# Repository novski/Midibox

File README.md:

VLR - Midibox
==============

Welcome 

Im Building Midibox Parts since 2010. All my Layouts and Parts are available here soon.

You can use all my designs under the TAPR License: http://www.ucapps.de/TAPR_Noncommercial_Hardware_License_v1.0.pdf.

the source of this work is to find at www.ucapps.com

You can find involved people at www.midibox.org/forums

Partslists are in Progress..

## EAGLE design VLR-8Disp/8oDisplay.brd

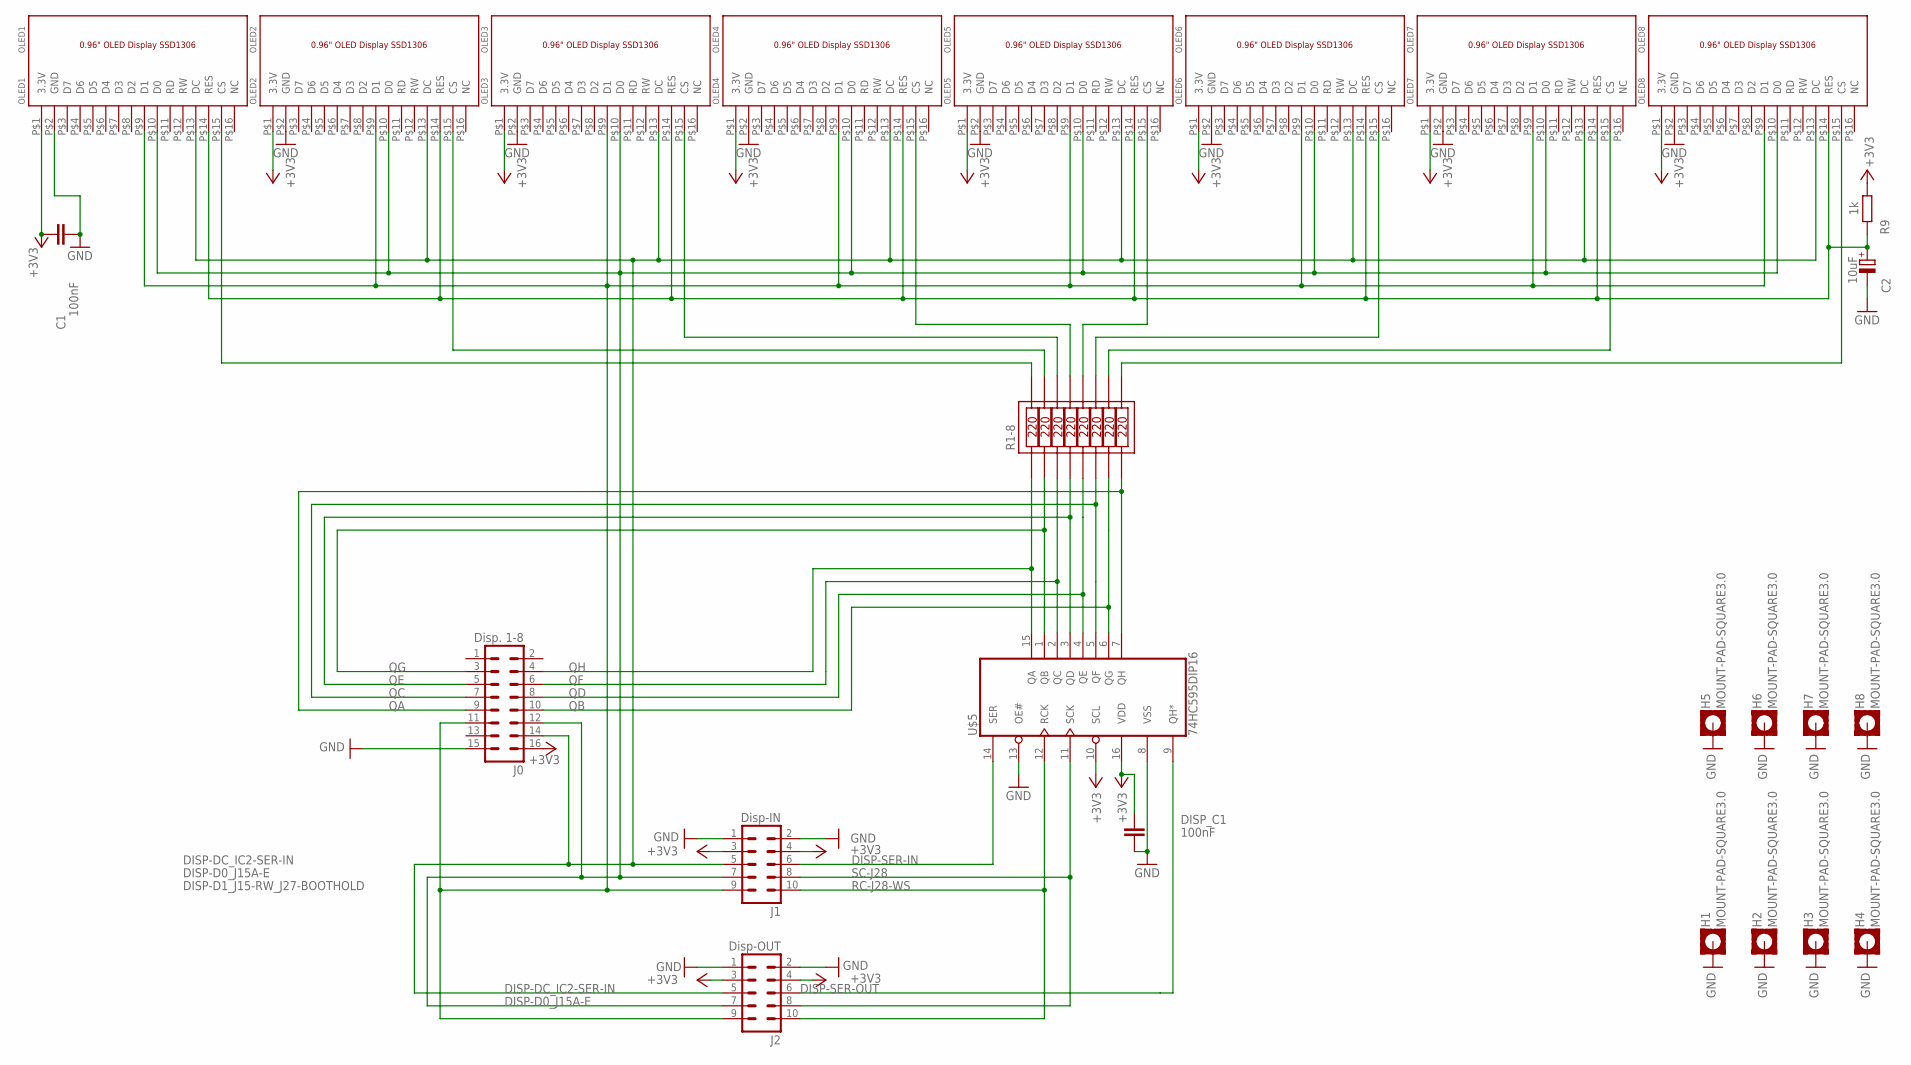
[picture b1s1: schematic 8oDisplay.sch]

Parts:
C1: 100nF; C5B3
C2: 10uF; E2,5-6
DISP_C1: 100nF; C5B3
H1, H2, H3, H4, H5, H6, H7, H8: MOUNT-PAD-SQUARE3.0; 3,0-PAD-SQUARE
J0: Disp. 1-8; ML16
J1: Disp-IN; ML10
J2: Disp-OUT; ML10
OLED1: OLED1; 0.96"
OLED2: OLED2; 0.96"
OLED3: OLED3; 0.96"
OLED4: OLED4; 0.96"
OLED5: OLED5; 0.96"
OLED6: OLED6; 0.96"
OLED7: OLED7; 0.96"
OLED8: OLED8; 0.96"
R1-8: 4116R; DIL16
R9: 1k; 0204/7
U$5: 74HC595DIP16; DIL16

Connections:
+3V3: C1.1, DISP_C1.1, J0.16, J1.3, J1.4, J2.3, J2.4, OLED1.P$1 (3.3V), OLED2.P$1 (3.3V), OLED3.P$1 (3.3V), OLED4.P$1 (3.3V), OLED5.P$1 (3.3V), OLED6.P$1 (3.3V), OLED7.P$1 (3.3V), OLED8.P$1 (3.3V), R9.2, U$5.10 (SCL), U$5.16 (VDD)
DISP-D0_J15A-E: J0.12, J1.7, J2.7, OLED1.P$10 (D0), OLED2.P$10 (D0), OLED3.P$10 (D0), OLED4.P$10 (D0), OLED5.P$10 (D0), OLED6.P$10 (D0), OLED7.P$10 (D0), OLED8.P$10 (D0)
DISP-D1_J15-RW_J27-BOOTHOLD: J0.11, J1.9, J2.9, OLED1.P$9 (D1), OLED2.P$9 (D1), OLED3.P$9 (D1), OLED4.P$9 (D1), OLED5.P$9 (D1), OLED6.P$9 (D1), OLED7.P$9 (D1), OLED8.P$9 (D1)
DISP-DC_IC2-SER-IN: J0.14, J1.5, J2.5, OLED1.P$13 (DC), OLED2.P$13 (DC), OLED3.P$13 (DC), OLED4.P$13 (DC), OLED5.P$13 (DC), OLED6.P$13 (DC), OLED7.P$13 (DC), OLED8.P$13 (DC)
DISP-SER-IN: J1.6, U$5.14 (SER)
DISP-SER-OUT: J2.6, U$5.9 (QH*)
GND: C1.2, C2.-, DISP_C1.2, H1.B3,0, H2.B3,0, H3.B3,0, H4.B3,0, H5.B3,0, H6.B3,0, H7.B3,0, H8.B3,0, J0.15, J1.1, J1.2, J2.1, J2.2, OLED1.P$2 (GND), OLED2.P$2 (GND), OLED3.P$2 (GND), OLED4.P$2 (GND), OLED5.P$2 (GND), OLED6.P$2 (GND), OLED7.P$2 (GND), OLED8.P$2 (GND), U$5.8 (VSS), U$5.13 (OE#)
QA: J0.9, R1-8.16, U$5.7 (QH)
QAA: OLED8.P$15 (CS), R1-8.8
QB: J0.10, R1-8.15, U$5.6 (QG)
QBB: OLED7.P$15 (CS), R1-8.7
QC: J0.7, R1-8.14, U$5.5 (QF)
QCC: OLED6.P$15 (CS), R1-8.6
QD: J0.8, R1-8.13, U$5.4 (QE)
QDD: OLED5.P$15 (CS), R1-8.5
QE: J0.5, R1-8.12, U$5.3 (QD)
QEE: OLED4.P$15 (CS), R1-8.4
QF: J0.6, R1-8.11, U$5.2 (QC)
QFF: OLED3.P$15 (CS), R1-8.3
QG: J0.3, R1-8.10, U$5.1 (QB)
QGG: OLED2.P$15 (CS), R1-8.2
QH: J0.4, R1-8.9, U$5.15 (QA)
QHH: OLED1.P$15 (CS), R1-8.1
RC-J28-WS: J1.10, J2.10, U$5.12 (RCK)
RST: C2.+, OLED1.P$14 (RES), OLED2.P$14 (RES), OLED3.P$14 (RES), OLED4.P$14 (RES), OLED5.P$14 (RES), OLED6.P$14 (RES), OLED7.P$14 (RES), OLED8.P$14 (RES), R9.1
SC-J28: J1.8, J2.8, U$5.11 (SCK)

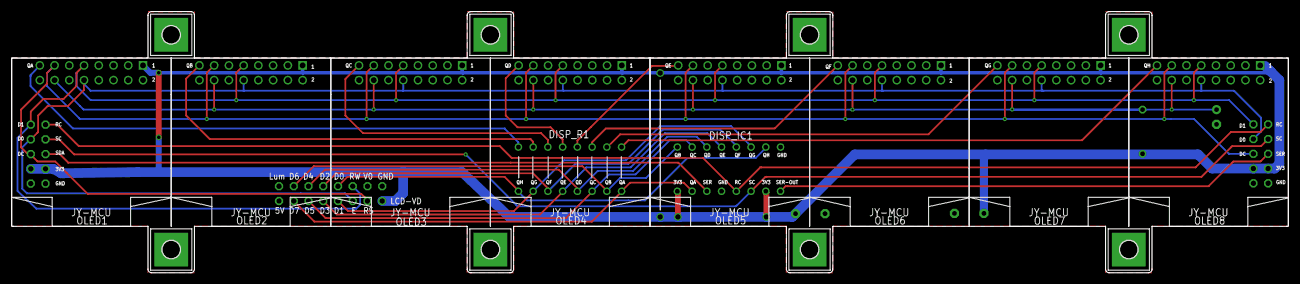
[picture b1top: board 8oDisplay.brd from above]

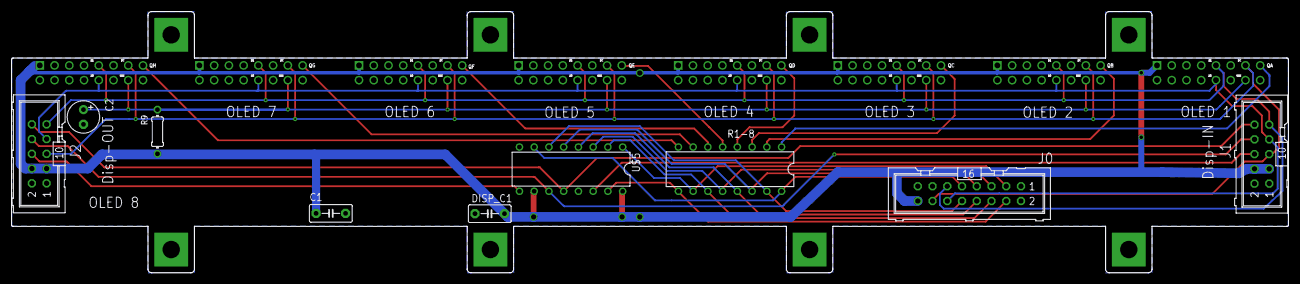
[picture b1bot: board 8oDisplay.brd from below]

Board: 2 copper layers, 220.0 x 45.0 mm, 28 parts (12 on the bottom side), 26 nets.

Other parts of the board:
U$1: X8ODISPLAY
U$2: VLRLAB
U$4: (C)T.KLOSE

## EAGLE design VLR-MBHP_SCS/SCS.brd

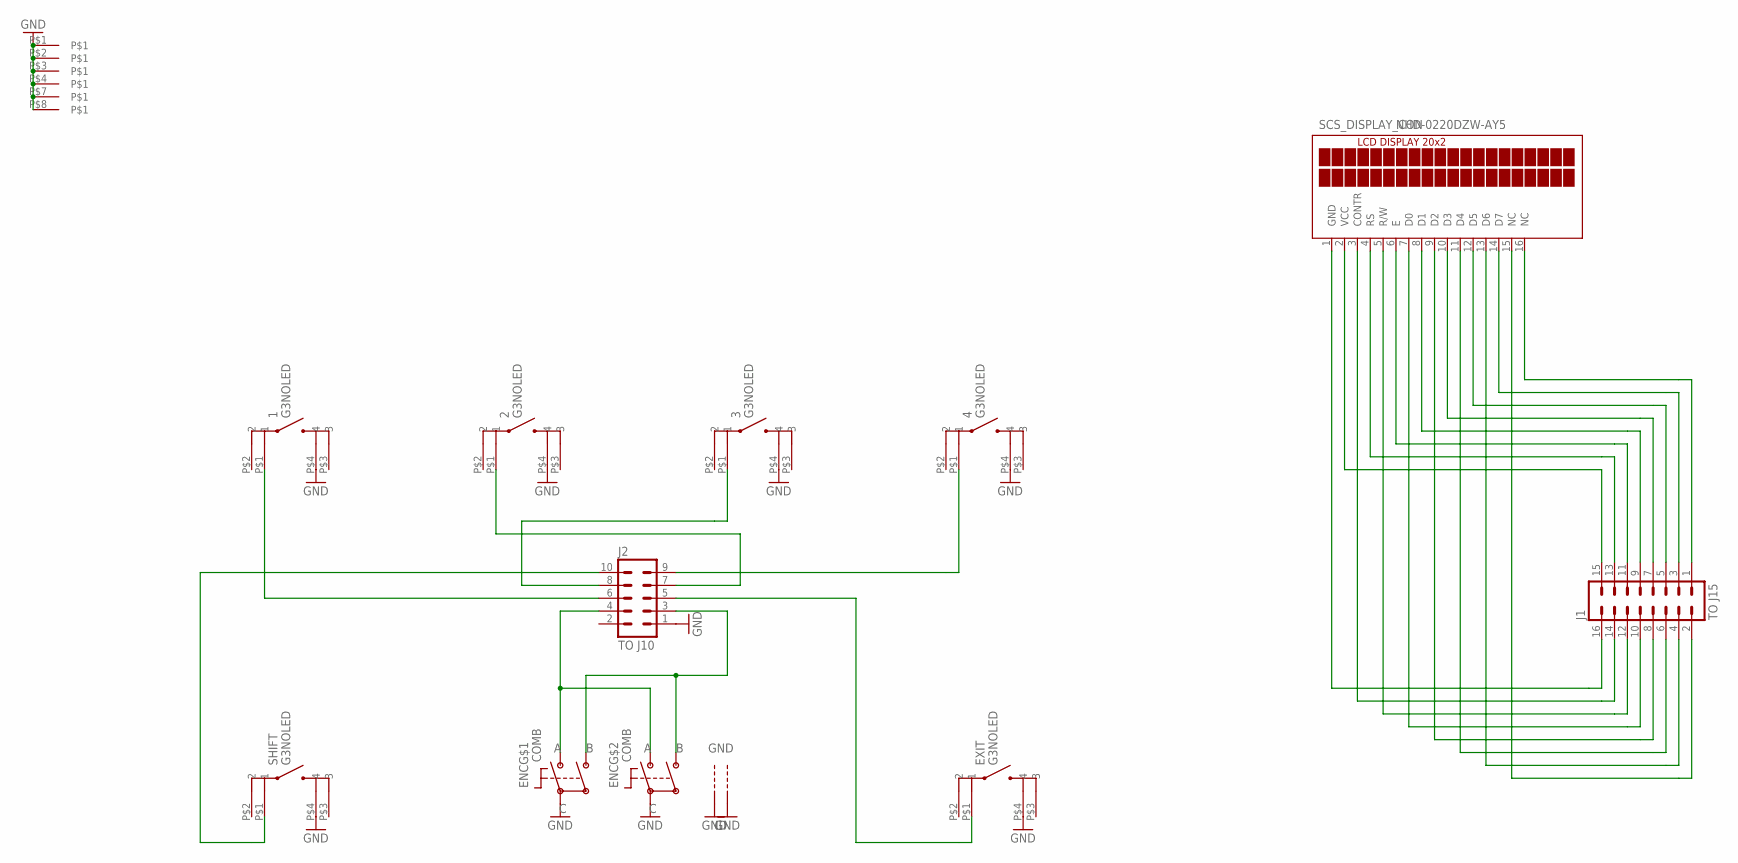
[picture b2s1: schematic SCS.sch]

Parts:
1, 2, 3, 4: G3NOLED
ENC: COMB; COMB_PEC11&STEC16
EXIT: G3NOLED
J1: TO J15; ML16
J2: TO J10; ML10
SCS_DISPLAY_CON: NHD-0220DZW-AY5
SHIFT: G3NOLED
U$2: MIDIBOX_FULL; MIDIBOX14X12

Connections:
GND: 1.P$4 (4), 2.P$4 (4), 3.P$4 (4), 4.P$4 (4), ENC.P$C, ENC.P$C1 (P$C), ENC.P$GND1, ENC.P$GND2, EXIT.P$4 (4), J2.1, SHIFT.P$4 (4), U$2.P$1, U$2.P$2, U$2.P$3, U$2.P$4, U$2.P$7, U$2.P$8
unnamed: J1.16, SCS_DISPLAY_CON.1 (GND)
unnamed: J1.15, SCS_DISPLAY_CON.2 (VCC)
unnamed: J1.14, SCS_DISPLAY_CON.3 (CONTR)
unnamed: J1.13, SCS_DISPLAY_CON.4 (RS)
unnamed: J1.12, SCS_DISPLAY_CON.5 (R/W)
unnamed: J1.11, SCS_DISPLAY_CON.6 (E)
unnamed: J1.10, SCS_DISPLAY_CON.7 (D0)
unnamed: J1.9, SCS_DISPLAY_CON.8 (D1)
unnamed: J1.8, SCS_DISPLAY_CON.9 (D2)
unnamed: J1.7, SCS_DISPLAY_CON.10 (D3)
unnamed: J1.6, SCS_DISPLAY_CON.11 (D4)
unnamed: J1.5, SCS_DISPLAY_CON.12 (D5)
unnamed: J1.4, SCS_DISPLAY_CON.13 (D6)
unnamed: J1.3, SCS_DISPLAY_CON.14 (D7)
unnamed: J1.2, SCS_DISPLAY_CON.15 (NC)
unnamed: J1.1, SCS_DISPLAY_CON.16 (NC)
unnamed: 1.P$1 (1), J2.6
unnamed: J2.10, SHIFT.P$1 (1)
unnamed: 2.P$1 (1), J2.7
unnamed: 3.P$1 (1), J2.8
unnamed: 4.P$1 (1), J2.9
unnamed: EXIT.P$1 (1), J2.5
unnamed: ENC.P$A, ENC.P$A1 (P$A), J2.4
unnamed: ENC.P$B, ENC.P$B1 (P$B), J2.3

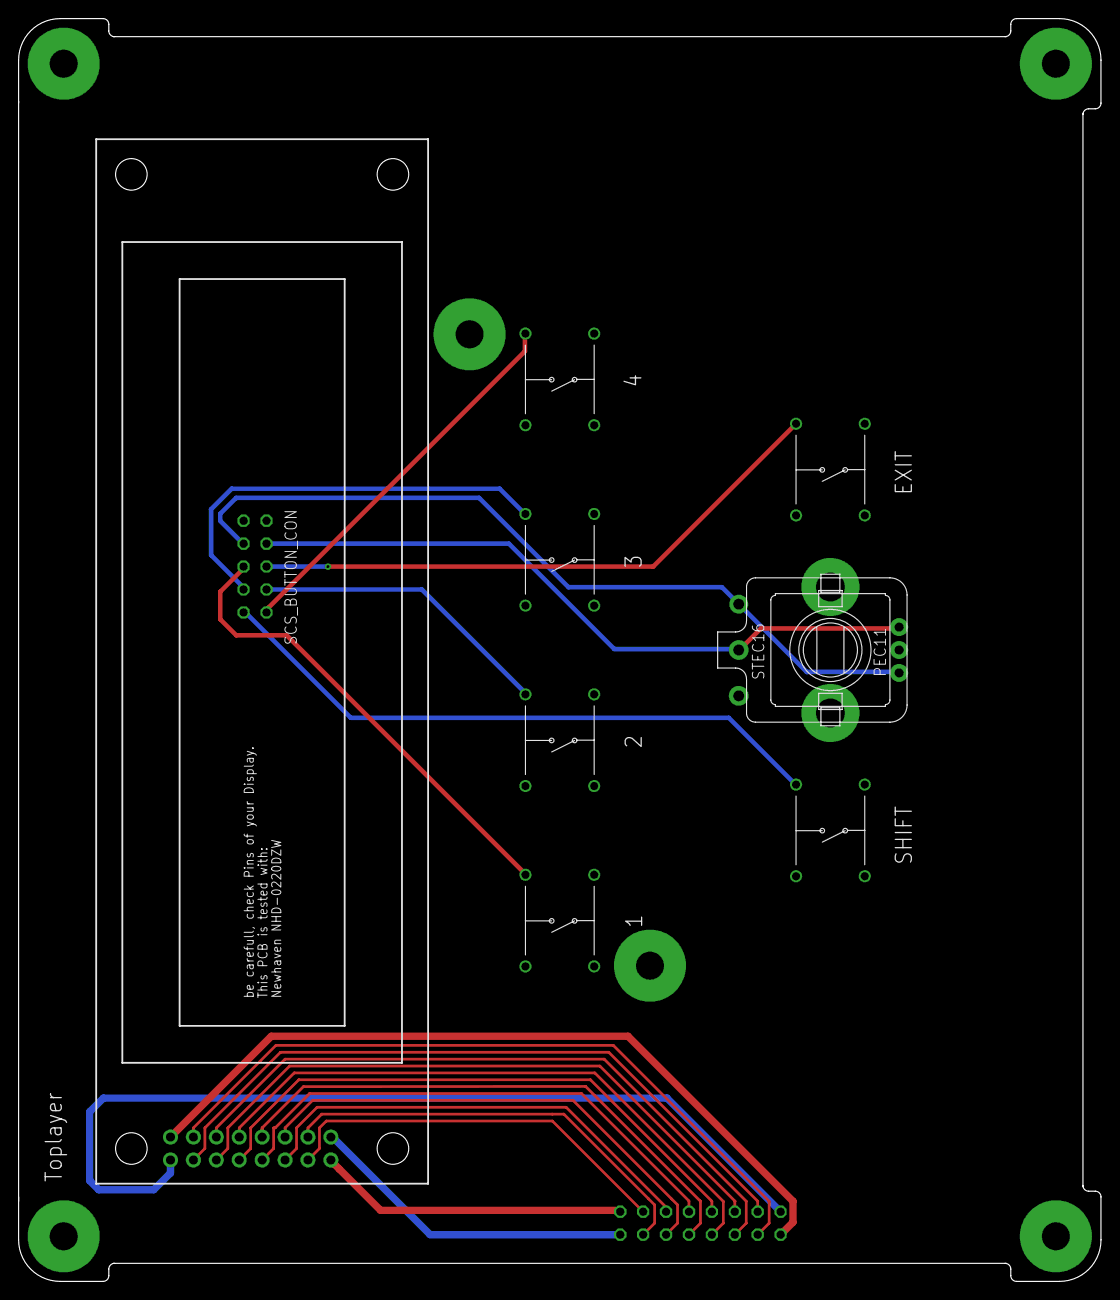
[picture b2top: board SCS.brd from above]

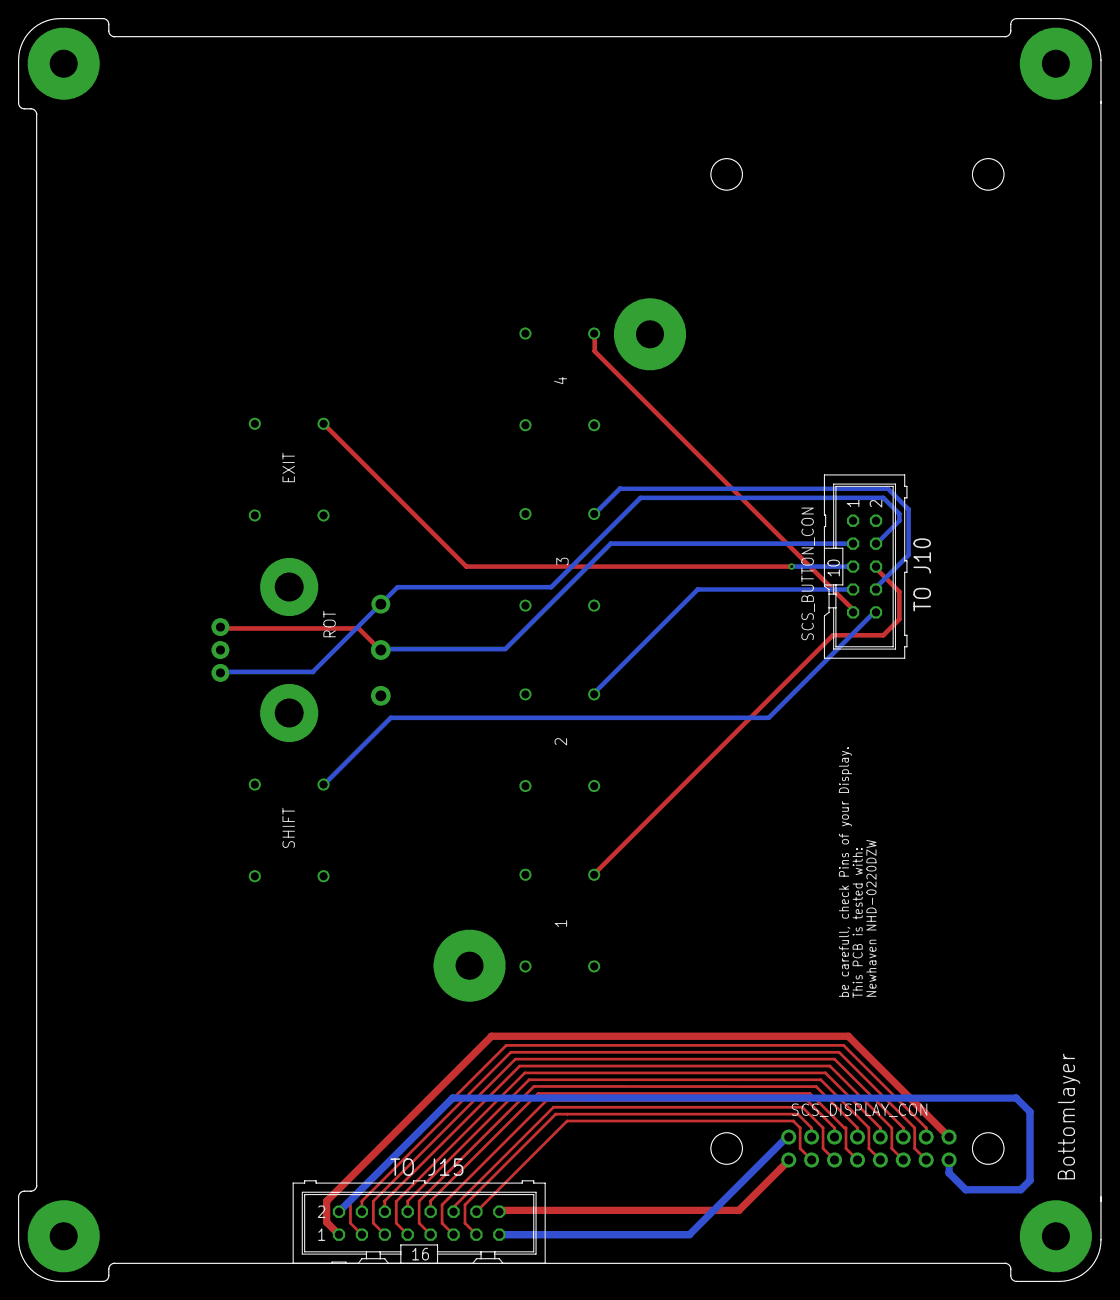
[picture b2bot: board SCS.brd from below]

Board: 2 copper layers, 120.0 x 140.0 mm, 17 parts (5 on the bottom side), 25 nets.

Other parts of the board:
U$3, U$5: (C)T.KLOSE
U$4, U$12: SCS
U$6, U$11: VLRLAB

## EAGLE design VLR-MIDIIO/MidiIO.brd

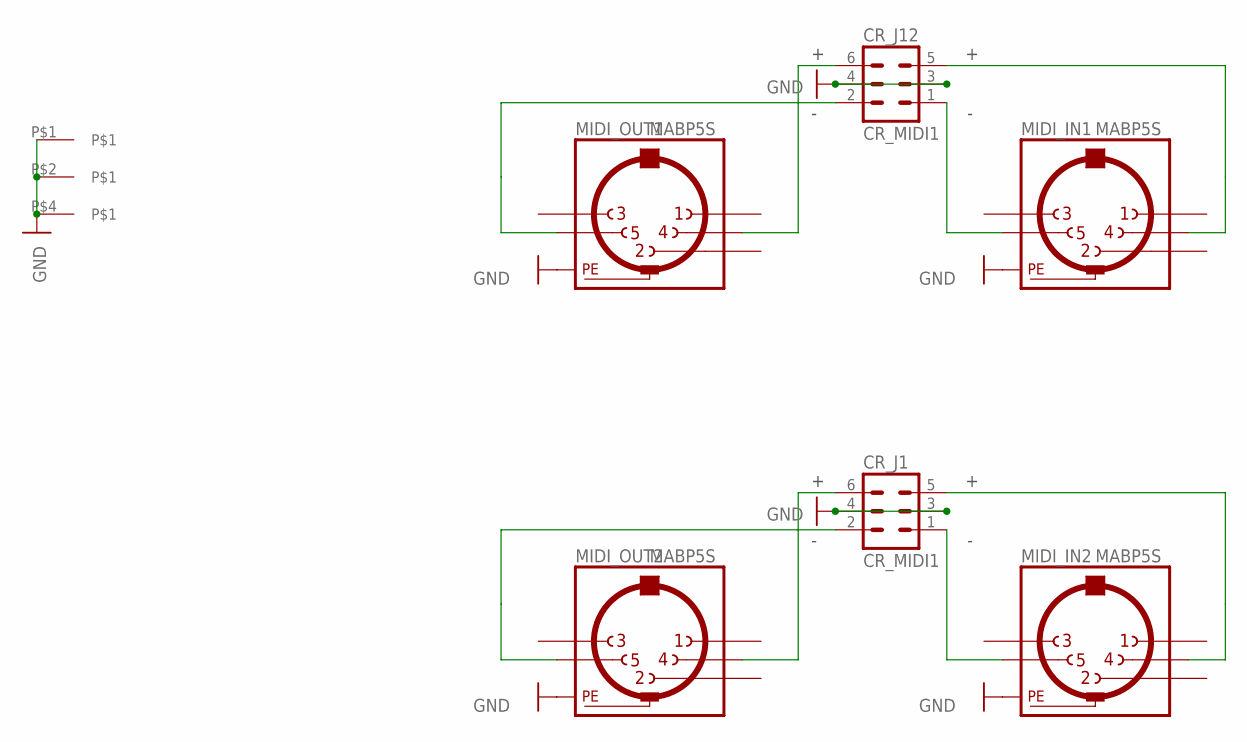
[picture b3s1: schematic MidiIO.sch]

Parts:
CR_J1, CR_J12: CR_MIDI1; ML6
MIDI_IN1, MIDI_IN2: MABP5S
MIDI_OUT1, MIDI_OUT2: MABP5S
U$2: MIDIBOX_HALF_FRONTLINE; MIDIBOX14X6-FRONTLINE

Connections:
CR_M1+: CR_J12.5, MIDI_IN1.4
CR_M1+1: CR_J1.5, MIDI_IN2.4
CR_M1-: CR_J12.1, MIDI_IN1.5
CR_M1-1: CR_J1.1, MIDI_IN2.5
GND: CR_J1.3, CR_J1.4, CR_J12.3, CR_J12.4, MIDI_IN1.PE, MIDI_IN1.PE@ (PE), MIDI_IN2.PE, MIDI_IN2.PE@ (PE), MIDI_OUT1.PE, MIDI_OUT1.PE@ (PE), MIDI_OUT2.PE, MIDI_OUT2.PE@ (PE), U$2.P$1, U$2.P$2, U$2.P$4
unnamed: CR_J1.6, MIDI_OUT2.4
unnamed: CR_J1.2, MIDI_OUT2.5
unnamed: CR_J12.6, MIDI_OUT1.4
unnamed: CR_J12.2, MIDI_OUT1.5

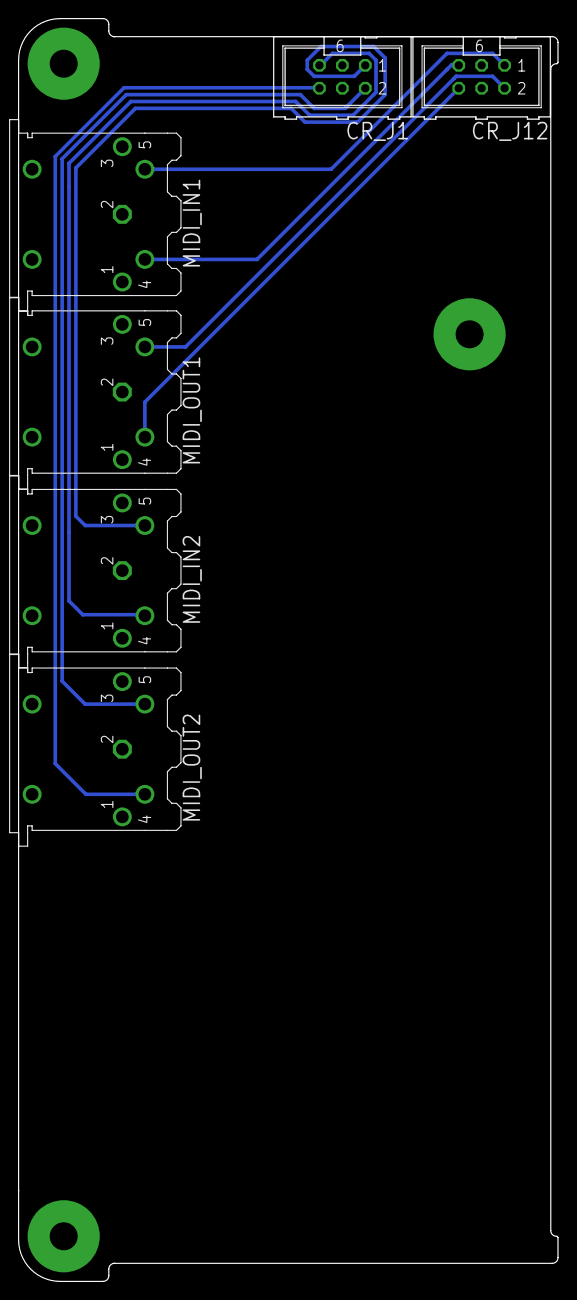
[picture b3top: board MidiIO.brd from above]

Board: 2 copper layers, 59.8 x 140.0 mm, 7 parts (0 on the bottom side), 9 nets.

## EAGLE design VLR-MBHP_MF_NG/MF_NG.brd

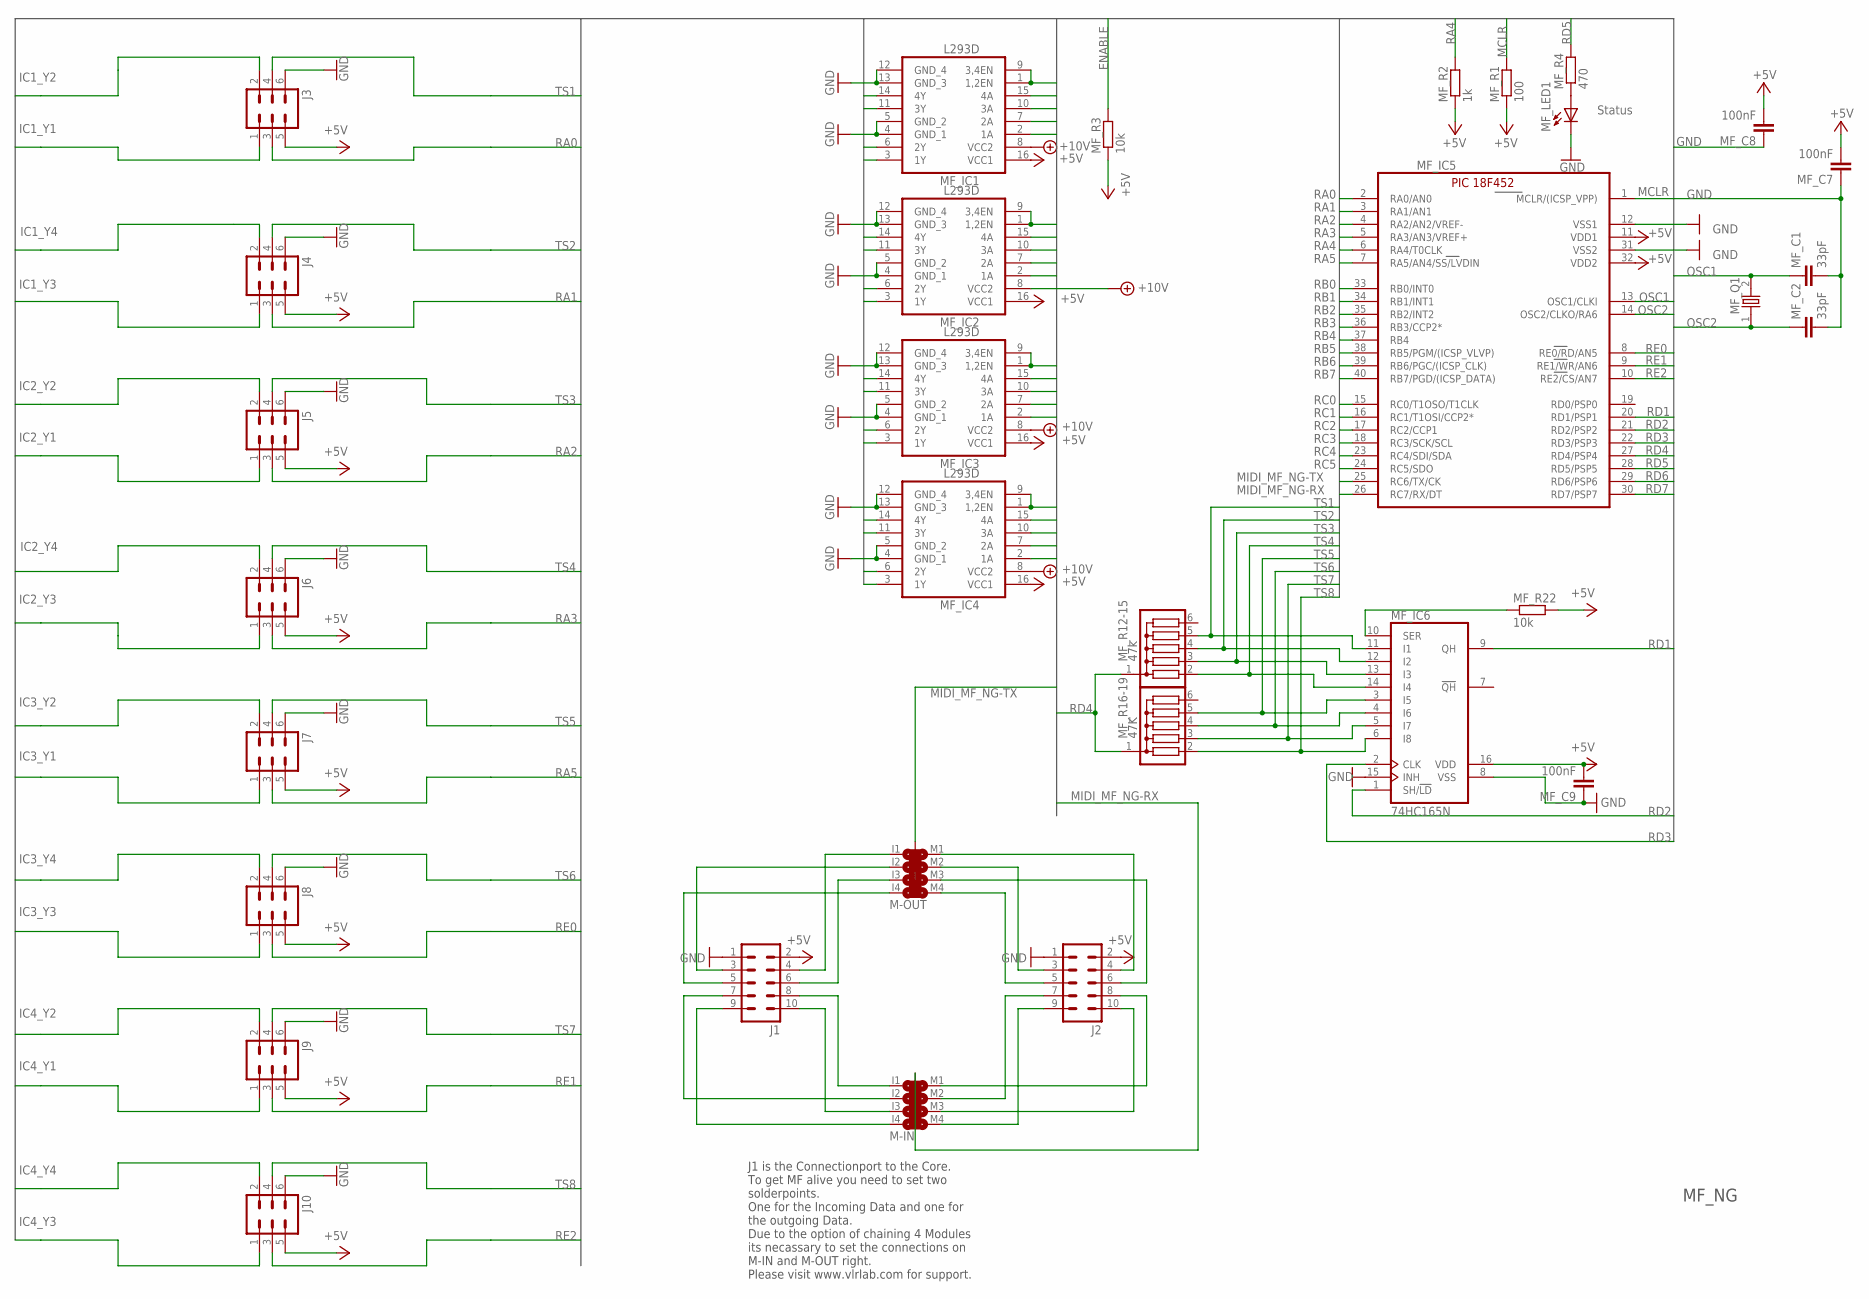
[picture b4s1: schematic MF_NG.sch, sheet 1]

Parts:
J1, J2: ML10ML10_TEXTFRONT; ML10_TEXTFRONT
J3, J4, J5, J6, J7, J8, J9, J10: ML6
M-IN: SJ2X4MIDI; SJ_2X4MIDI
M-OUT: SJ2X4MIDI; SJ_2X4MIDI
MF_C1, MF_C2: 33pF; C025-030X050
MF_C7, MF_C8, MF_C9: 100nF; C025-025X050
MF_IC1, MF_IC2, MF_IC3, MF_IC4: L293D; DIL16
MF_IC5: PIC18F452; DIL40
MF_IC6: 74HC165N; DIL16
MF_LED1: Status; LED3MM
MF_Q1: ECS-100-20-4X-DU; HC-49/USX
MF_R1: 100; 0204/7
MF_R2: 1k; 0204/7
MF_R3, MF_R22: 10k; 0204/7
MF_R4: 470; 0204/7
MF_R12-15: 47k; SIL6
MF_R16-19: 47K; SIL6

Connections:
+5V: J1.2, J2.2, J3.5, J4.5, J5.5, J6.5, J7.5, J8.5, J9.5, J10.5, MF_C7.2, MF_C8.2, MF_C9.2, MF_IC1.16 (VCC1), MF_IC2.16 (VCC1), MF_IC3.16 (VCC1), MF_IC4.16 (VCC1), MF_IC5.11 (VDD1), MF_IC5.32 (VDD2), MF_IC6.16 (VDD), MF_R1.1, MF_R2.1, MF_R3.1, MF_R22.2; also elsewhere on the board
+10V: MF_IC1.8 (VCC2), MF_IC2.8 (VCC2), MF_IC3.8 (VCC2), MF_IC4.8 (VCC2); also elsewhere on the board
ENABLE: MF_IC1.1 (1,2EN), MF_IC1.9 (3,4EN), MF_IC2.1 (1,2EN), MF_IC2.9 (3,4EN), MF_IC3.1 (1,2EN), MF_IC3.9 (3,4EN), MF_IC4.1 (1,2EN), MF_IC4.9 (3,4EN), MF_R3.2
GND: J1.1, J2.1, J3.6, J4.6, J5.6, J6.6, J7.6, J8.6, J9.6, J10.6, MF_C1.2, MF_C2.2, MF_C7.1, MF_C8.1, MF_C9.1, MF_IC1.4 (GND_1), MF_IC1.5 (GND_2), MF_IC1.12 (GND_4), MF_IC1.13 (GND_3), MF_IC2.4 (GND_1), MF_IC2.5 (GND_2), MF_IC2.12 (GND_4), MF_IC2.13 (GND_3), MF_IC3.4 (GND_1), MF_IC3.5 (GND_2), MF_IC3.12 (GND_4), MF_IC3.13 (GND_3), MF_IC4.4 (GND_1), MF_IC4.5 (GND_2), MF_IC4.12 (GND_4), MF_IC4.13 (GND_3), MF_IC5.12 (VSS1), MF_IC5.31 (VSS2), MF_IC6.8 (VSS), MF_IC6.15 (INH), MF_LED1.K (C); also elsewhere on the board
IC1_Y1: J3.1, MF_IC1.3 (1Y)
IC1_Y2: J3.2, MF_IC1.6 (2Y)
IC1_Y3: J4.1, MF_IC1.11 (3Y)
IC1_Y4: J4.2, MF_IC1.14 (4Y)
IC2_Y1: J5.1, MF_IC2.3 (1Y)
IC2_Y2: J5.2, MF_IC2.6 (2Y)
IC2_Y3: J6.1, MF_IC2.11 (3Y)
IC2_Y4: J6.2, MF_IC2.14 (4Y)
IC3_Y1: J7.1, MF_IC3.3 (1Y)
IC3_Y2: J7.2, MF_IC3.6 (2Y)
IC3_Y3: J8.1, MF_IC3.11 (3Y)
IC3_Y4: J8.2, MF_IC3.14 (4Y)
IC4_Y1: J9.1, MF_IC4.3 (1Y)
IC4_Y2: J9.2, MF_IC4.6 (2Y)
IC4_Y3: J10.1, MF_IC4.11 (3Y)
IC4_Y4: J10.2, MF_IC4.14 (4Y)
MCLR: MF_IC5.1 (MCLR/(ICSP_VPP)), MF_R1.2
MIDI_MF_NG-RX: M-IN.0, MF_IC5.26 (RC7/RX/DT)
MIDI_MF_NG-TX: M-OUT.0, MF_IC5.25 (RC6/TX/CK)
unnamed: MF_IC6.10 (SER), MF_R22.1
unnamed: MF_LED1.A, MF_R4.1
unnamed: J1.4, M-OUT.I1
unnamed: J1.3, M-OUT.I2
unnamed: J1.6, M-OUT.I3
unnamed: J1.5, M-OUT.I4
unnamed: J2.4, M-OUT.M1
unnamed: J2.3, M-OUT.M2
unnamed: J2.6, M-OUT.M3
unnamed: J2.5, M-OUT.M4
unnamed: J1.8, M-IN.I1
unnamed: J1.7, M-IN.I2
unnamed: J1.10, M-IN.I3
unnamed: J1.9, M-IN.I4
unnamed: J2.8, M-IN.M1
unnamed: J2.7, M-IN.M2
unnamed: J2.10, M-IN.M3
unnamed: J2.9, M-IN.M4
OSC1: MF_C1.1, MF_IC5.13 (OSC1/CLKI), MF_Q1.2
OSC2: MF_C2.1, MF_IC5.14 (OSC2/CLKO/RA6), MF_Q1.1
RA0: J3.3, MF_IC5.2 (RA0/AN0)
RA1: J4.3, MF_IC5.3 (RA1/AN1)
RA2: J5.3, MF_IC5.4 (RA2/AN2/VREF-)
RA3: J6.3, MF_IC5.5 (RA3/AN3/VREF+)
RA4: MF_IC5.6 (RA4/T0CLK), MF_R2.2
RA5: J7.3, MF_IC5.7 (RA5/AN4/SS/LVDIN)
RB0: MF_IC2.15 (4A), MF_IC5.33 (RB0/INT0)
RB1: MF_IC2.10 (3A), MF_IC5.34 (RB1/INT1)
RB2: MF_IC2.7 (2A), MF_IC5.35 (RB2/INT2)
RB3: MF_IC2.2 (1A), MF_IC5.36 (RB3/CCP2*)
RB4: MF_IC1.15 (4A), MF_IC5.37 (RB4)
RB5: MF_IC1.10 (3A), MF_IC5.38 (RB5/PGM/(ICSP_VLVP))
RB6: MF_IC1.7 (2A), MF_IC5.39 (RB6/PGC/(ICSP_CLK))
RB7: MF_IC1.2 (1A), MF_IC5.40 (RB7/PGD/(ICSP_DATA))
RC0: MF_IC4.15 (4A), MF_IC5.15 (RC0/T1OSO/T1CLK)
RC1: MF_IC4.10 (3A), MF_IC5.16 (RC1/T1OSI/CCP2*)
RC2: MF_IC4.7 (2A), MF_IC5.17 (RC2/CCP1)
RC3: MF_IC4.2 (1A), MF_IC5.18 (RC3/SCK/SCL)
RC4: MF_IC3.15 (4A), MF_IC5.23 (RC4/SDI/SDA)
RC5: MF_IC3.10 (3A), MF_IC5.24 (RC5/SDO)
RD1: MF_IC5.20 (RD1/PSP1), MF_IC6.9 (QH)
RD2: MF_IC5.21 (RD2/PSP2), MF_IC6.1 (SH/!LD)
RD3: MF_IC5.22 (RD3/PSP3), MF_IC6.2 (CLK)
RD4: MF_IC5.27 (RD4/PSP4), MF_R12-15.1, MF_R16-19.1
RD5: MF_IC5.28 (RD5/PSP5), MF_R4.2
RD6: MF_IC3.7 (2A), MF_IC5.29 (RD6/PSP6)
RD7: MF_IC3.2 (1A), MF_IC5.30 (RD7/PSP7)
RE0: J8.3, MF_IC5.8 (RE0/RD/AN5)
RE1: J9.3, MF_IC5.9 (RE1/WR/AN6)
RE2: J10.3, MF_IC5.10 (RE2/CS/AN7)
TS1: J3.4, MF_IC6.11 (I1), MF_R12-15.5
TS2: J4.4, MF_IC6.12 (I2), MF_R12-15.4
TS3: J5.4, MF_IC6.13 (I3), MF_R12-15.3
TS4: J6.4, MF_IC6.14 (I4), MF_R12-15.2
TS5: J7.4, MF_IC6.3 (I5), MF_R16-19.5
TS6: J8.4, MF_IC6.4 (I6), MF_R16-19.4
TS7: J9.4, MF_IC6.5 (I7), MF_R16-19.3
TS8: J10.4, MF_IC6.6 (I8), MF_R16-19.2

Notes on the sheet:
MF_NG
J1 is the Connectionport to the Core. To get MF alive you need to set two solderpoints. One for the Incoming Data and one for the outgoing Data. Due to the option of chaining 4 Modules its necassary to set the connections on M-IN and M-OUT right. Please visit www.vlrlab.com for support.

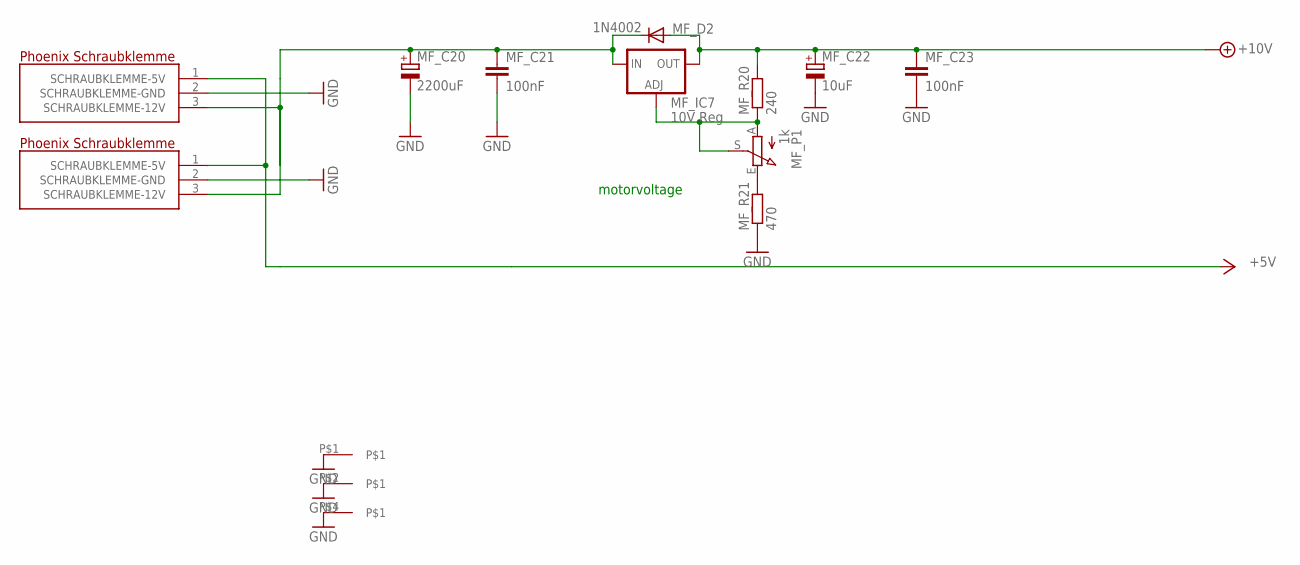
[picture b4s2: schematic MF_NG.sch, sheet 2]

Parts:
KLEMME1, KLEMME2: PT-1.5/3; PT-1.5/3-5.0
MF_C20: 2200uF; E5-13
MF_C21, MF_C23: 100nF; C025-025X050
MF_C22: 10uF; E2,5-6E
MF_D2: 1N4002; D040-10
MF_IC7: 10V Reg; 317TS
MF_P1: 1k; 6MM_V
MF_R20: 240; 0204/7
MF_R21: 470; 0204/7
U$3: MIDIBOX_HALF; MIDIBOX14X6

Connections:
+5V: KLEMME1.1 (SCHRAUBKLEMME-5V), KLEMME2.1 (SCHRAUBKLEMME-5V); also elsewhere on the board
+10V: MF_C22.+, MF_C23.1, MF_D2.A, MF_IC7.2 (OUT), MF_R20.2; also elsewhere on the board
+12V: KLEMME1.3 (SCHRAUBKLEMME-12V), KLEMME2.3 (SCHRAUBKLEMME-12V), MF_C20.+, MF_C21.1, MF_D2.C, MF_IC7.3 (IN)
GND: KLEMME1.2 (SCHRAUBKLEMME-GND), KLEMME2.2 (SCHRAUBKLEMME-GND), MF_C20.-, MF_C21.2, MF_C22.-, MF_C23.2, MF_R21.1, U$3.P$1, U$3.P$2, U$3.P$4; also elsewhere on the board
unnamed: MF_IC7.1 (ADJ), MF_P1.A, MF_P1.S, MF_R20.1
unnamed: MF_P1.E, MF_R21.2

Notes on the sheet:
motorvoltage

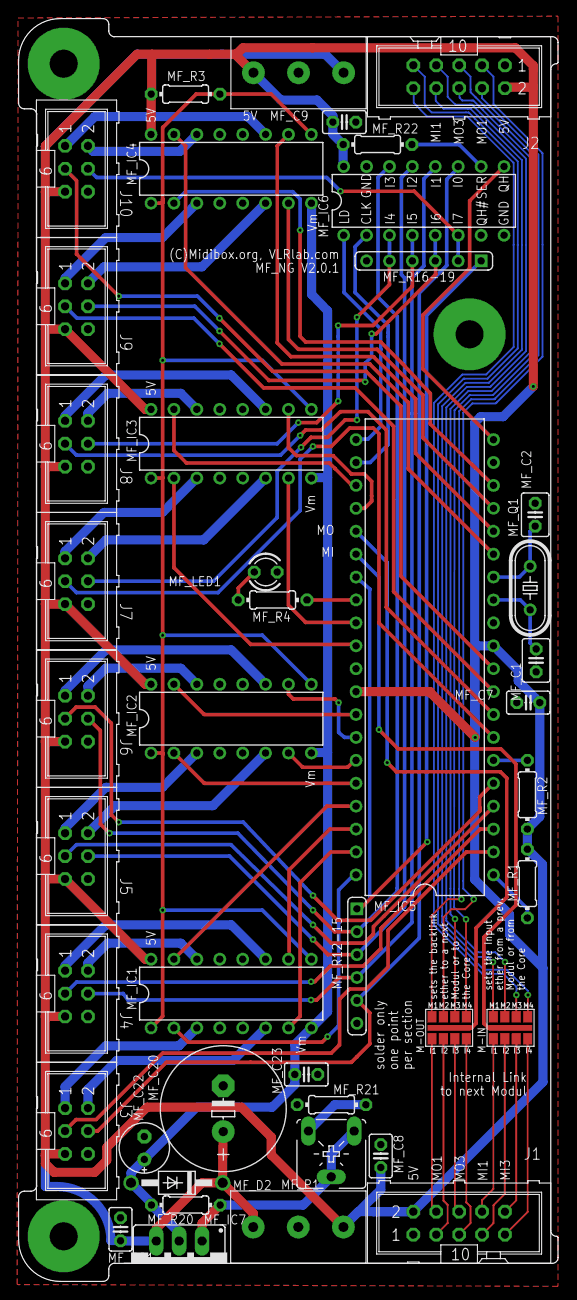
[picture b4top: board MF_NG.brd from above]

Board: 2 copper layers, 59.8 x 140.0 mm, 46 parts (1 on the bottom side), 84 nets.

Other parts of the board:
U$5: VLRLAB_SMAL
U$6: VLRLAB

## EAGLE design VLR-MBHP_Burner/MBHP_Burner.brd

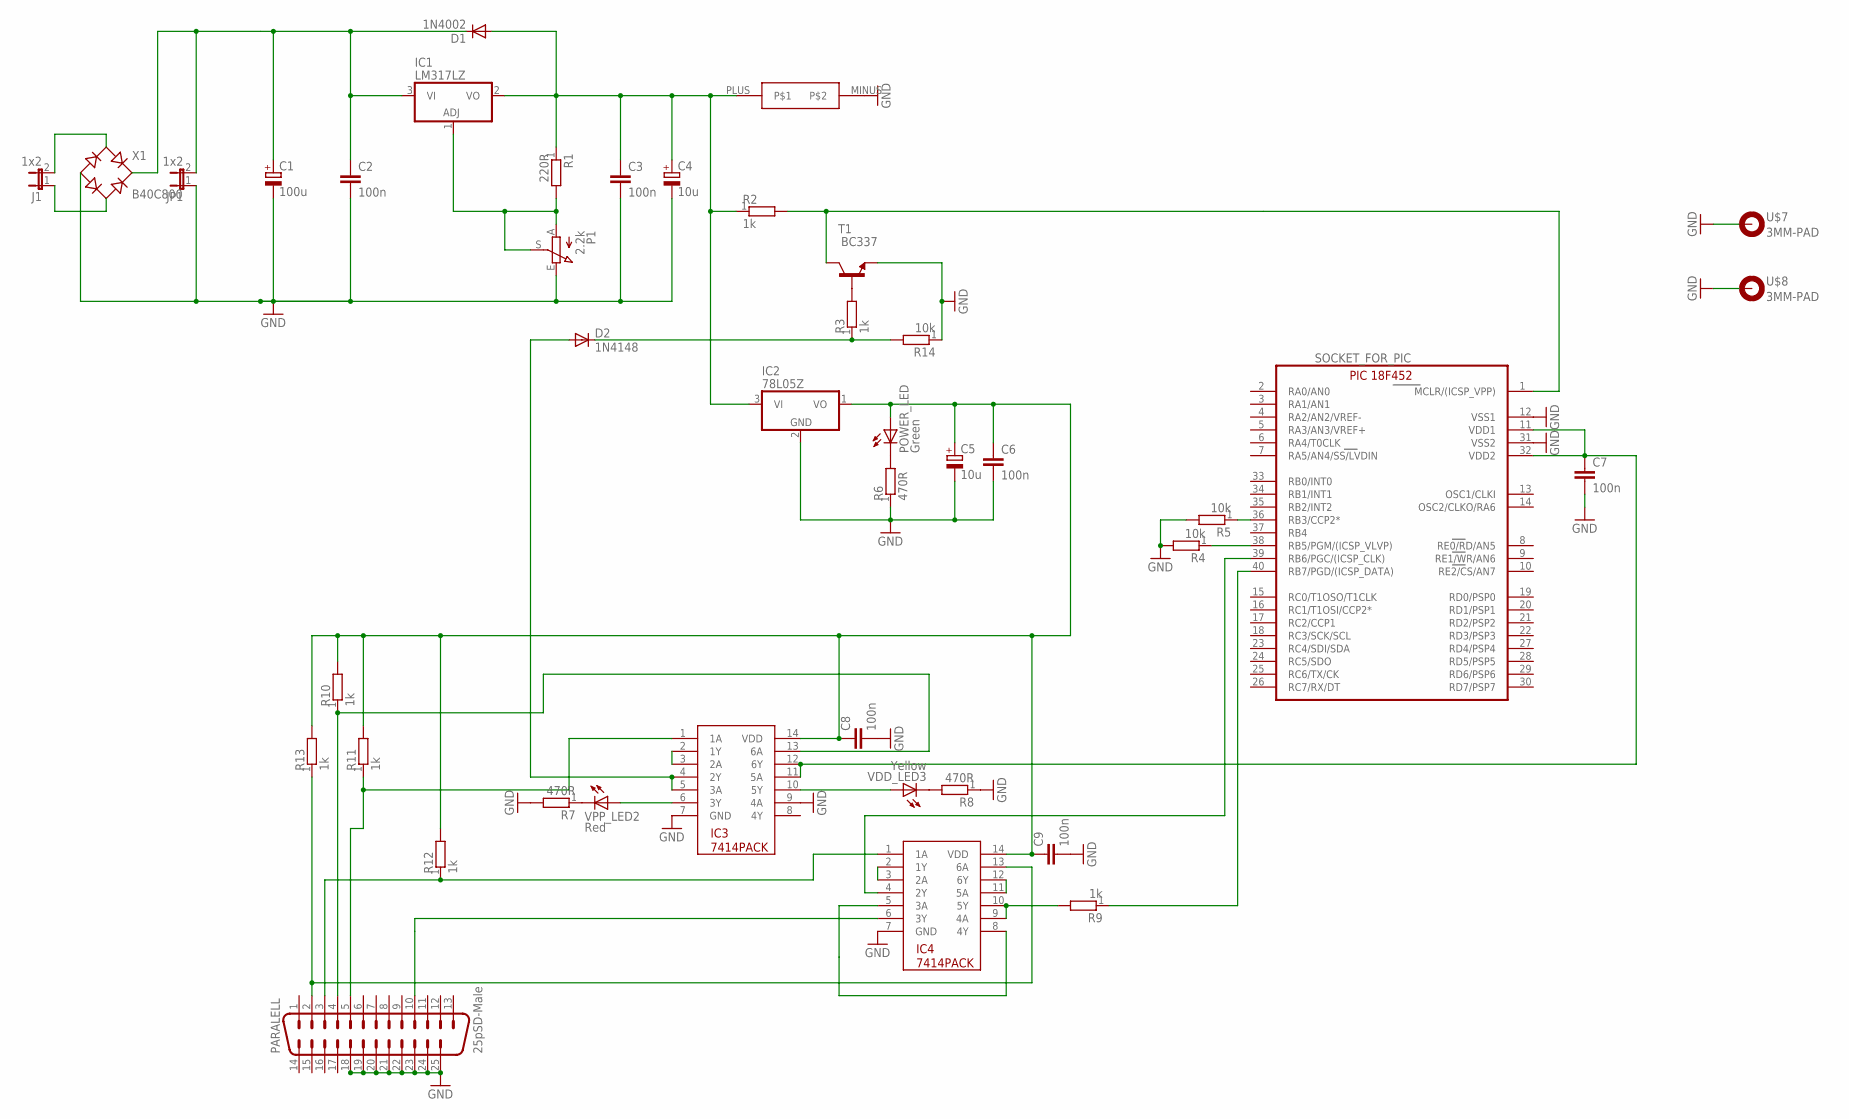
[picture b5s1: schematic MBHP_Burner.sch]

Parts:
C1: 100u; E5-8,5
C2, C3, C6, C7, C8, C9: 100n; C5B2.5
C4, C5: 10u; E2,5-7
D1: 1N4002; D040-10
D2: 1N4148; DO35-7
IC1: LM317LZ; TO92
IC2: 78L05Z; TO92
IC3, IC4: 7414PACK; DIL14
J1: 1x2; JP1
J2: MEASUREING-POINT12.5V; MEASURINGPOINT
JP1: 1x2; JP1
P1: 2.2k; 6MM_V
PARALELL: 25pSD-Male; M25HP
POWER_LED: Green; LED3MM
R1: 220R; R-12MM
R2, R3, R9, R10, R11, R12, R13: 1k; R-12MM
R4, R5, R14: 10k; R-12MM
R6, R7, R8: 470R; R-12MM
SOCKET_FOR_PIC: PIC18F4X2DIL40; DIL40
T1: BC337; TO92
U$7, U$8: 3MM-PAD
VDD_LED3: Yellow; LED3MM
VPP_LED2: Red; LED3MM
X1: B40C800; RB1A

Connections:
GND: C1.-, C2.2, C3.2, C4.-, C5.-, C6.2, C7.2, C8.2, C9.2, IC2.2 (GND), IC3.7 (GND), IC3.9 (4A), IC4.7 (GND), J2.MINUS, JP1.1, P1.E, PARALELL.18, PARALELL.19, PARALELL.20, PARALELL.21, PARALELL.22, PARALELL.23, PARALELL.24, PARALELL.25, R4.2, R5.2, R6.1, R7.2, R8.1, R14.1, SOCKET_FOR_PIC.12 (VSS1), SOCKET_FOR_PIC.31 (VSS2), T1.1 (E), U$7.B3, U$8.B3, X1.-
unnamed: R2.2, SOCKET_FOR_PIC.1 (MCLR/(ICSP_VPP)), T1.3 (C)
unnamed: IC1.1 (ADJ), P1.A, P1.S, R1.2
unnamed: POWER_LED.K (C), R6.2
unnamed: C3.1, C4.+, D1.A, IC1.2 (VO), IC2.3 (VI), J2.PLUS, R1.1, R2.1
unnamed: C1.+, C2.1, D1.C, IC1.3 (VI), JP1.2, X1.+
unnamed: IC4.11 (5A), IC4.12 (6Y)
unnamed: R3.2, T1.2 (B)
unnamed: D2.C, R3.1, R14.2
unnamed: R5.1, SOCKET_FOR_PIC.36 (RB3/CCP2*)
unnamed: R4.1, SOCKET_FOR_PIC.38 (RB5/PGM/(ICSP_VLVP))
unnamed: C5.+, C6.1, C8.1, C9.1, IC2.1 (VO), IC3.14 (VDD), IC4.14 (VDD), POWER_LED.A, R10.2, R11.2, R12.2, R13.2
unnamed: IC3.13 (6A), PARALELL.4, R10.1
unnamed: IC4.13 (6A), PARALELL.2, R13.1
unnamed: IC4.1 (1A), PARALELL.3, R12.1
unnamed: IC3.1 (1A), PARALELL.5, R11.1
unnamed: IC3.2 (1Y), IC3.3 (2A)
unnamed: D2.A, IC3.4 (2Y), IC3.5 (3A)
unnamed: C7.1, IC3.11 (5A), IC3.12 (6Y), SOCKET_FOR_PIC.11 (VDD1), SOCKET_FOR_PIC.32 (VDD2)
unnamed: IC3.6 (3Y), VPP_LED2.A
unnamed: IC3.10 (5Y), VDD_LED3.A
unnamed: R7.1, VPP_LED2.K (C)
unnamed: R8.2, VDD_LED3.K (C)
unnamed: IC4.2 (1Y), IC4.3 (2A)
unnamed: IC4.4 (2Y), SOCKET_FOR_PIC.39 (RB6/PGC/(ICSP_CLK))
unnamed: IC4.5 (3A), IC4.8 (4Y)
unnamed: IC4.6 (3Y), PARALELL.10
unnamed: IC4.9 (4A), IC4.10 (5Y), R9.2
unnamed: R9.1, SOCKET_FOR_PIC.40 (RB7/PGD/(ICSP_DATA))
unnamed: J1.2, X1.AC1
unnamed: J1.1, X1.AC2

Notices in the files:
parts and their libraries:
Frames_VLR: © VLRlab Hörler
